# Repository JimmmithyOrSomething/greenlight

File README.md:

greenlight quantum number genorator

I've always been so interested in how nothing in our world is truly random but we still can never predict everything about any situation beucase all our information is relative. And I've always found it so cool how things on a quantum scale don't have to follow the same rules that we do like existing in one place at a time or needing a reason for something to happen. I built greenlight to show myself a little bit about how existance really works by generating a truly random number using a beam of light.

This is a quantum number generator, basically because nothing in our world can be random on a large scale this is a device that uses a beam of light split into two via a special panel which means exactly half of the photons go one way and half go the other. This means that when one photon hits the panel it both goes through and bounces off (existing in a super position)until it is read by one of the photo diodes at which point that position becomes real (like schrodinger's cat but with light instead of a sensor looking for decay) And this can generate a fully random number that no computer could ever guess because it doesn’t follow our idea of cause and effect.

| item | quantity | price(total)  | info | link
| ------- | --- | --- |--- | --- |
| laser | 1 | 2  |The brains of the system| [here](https://www.aliexpress.us/item/3256808453111185.html?spm=a2g0o.productlist.main.35.744fqgtvqgtvPm&algo_pvid=f6886ff8-4b31-4075-8188-40aaf95708aa&algo_exp_id=f6886ff8-4b31-4075-8188-40aaf95708aa-34&pdp_ext_f=%7B%22order%22%3A%22-1%22%2C%22eval%22%3A%221%22%7D&pdp_npi=4%40dis%21USD%212.03%212.03%21%21%212.03%212.03%21%402101c72a17529456784327303e85bb%2112000046054694972%21sea%21US%210%21ABX&curPageLogUid=kv1oggH1eqMu&utparam-url=scene%3Asearch%7Cquery_from%3A) |
| photodioed|	5|	1|	Cheap photdiodes|	[here](https://www.aliexpress.us/item/3256806716614140.html?src=bing&aff_short_key=UneMJZVf&aff_platform=true&isdl=y&albch=shopping&acnt=135095331&isdl=y&albcp=555334313&albag=1297424920872946&slnk=&trgt=pla-2332888796630869&plac=&crea=81089116576383&netw=o&device=c&mtctp=e&utm_source=Bing&utm_medium=shopping&utm_campaign=PA_Bing_US_Pmax_Electronic_maxvalue_20250304_newstore&utm_content=US-ALL&utm_term=photodioed%20BPW34&msclkid=646af2a3190b163feb729ad8ca68c24f&gatewayAdapt=glo2usa)|
|PCB	|5|	23|	holds all my parts|	[here](https://jlcpcb.com/)|
|OP amp|	5|	6	|to make sure signal is readable|	[here](https://www.aliexpress.us/item/3256808626573500.html?spm=a2g0o.productlist.main.2.342a2183yR25hE&algo_pvid=02a50136-7563-4f8f-b229-f992b53c9055&algo_exp_id=02a50136-7563-4f8f-b229-f992b53c9055-1&pdp_ext_f=%7B%22order%22%3A%222%22%2C%22eval%22%3A%221%22%7D&pdp_npi=4%40dis%21USD%215.80%215.80%21%21%215.80%215.80%21%402103205117529457957094127e6313%2112000046772434171%21sea%21US%210%21ABX&curPageLogUid=N1vaMkOQOGpw&utparam-url=scene%3Asearch%7Cquery_from%3A)|
|filter|	1	|18 |	cheapest filter I can fild|	[here](https://www.amazon.com/Concept-ND1000000-20-Stops-Multi-Layer-Coatings/dp/B0CW3D2PMC/ref=sr_1_1_sspa?adgrpid=1332609823086002&dib=eyJ2IjoiMSJ9.GbUoWurGez8xOJK7iHyZM6mhiLBdfH48SLrOkIF-YmTWcl3uBkbn52Y6AGVJasMP8Lmqf6YZ6I2f6fziKpwVHIBvxAwMenP9v0XX4e_BqgdHE4egFfyvJ2jyUc7t6Rfa1wY0C-v8xH4QZoVuCoLrwVx_2d1sE8cAqdTrmQmJrvVp6806LEs6a12m2_RrR0SjqPXmmdagr7ZUKq4f7kg7F52Zq2PsGZmk6Sk268Yzays.Db1pMk2CLClHrpgIouHmAGj_aQwpIjryEDxz2_Z2RQA&dib_tag=se&hvadid=83288427977273&hvbmt=be&hvdev=c&hvlocphy=103047&hvnetw=o&hvqmt=e&hvtargid=kwd-83289171702520%3Aloc-190&hydadcr=7692_13723063&keywords=20%2Bstop%2Bnd%2Bfilter&mcid=c65c21dc498d3d9291255622b3970efc&msclkid=84e1ac82a5c812d00597c4f970b71ac8&qid=1752946051&sr=8-1-spons&sp_csd=d2lkZ2V0TmFtZT1zcF9hdGY&th=1)|

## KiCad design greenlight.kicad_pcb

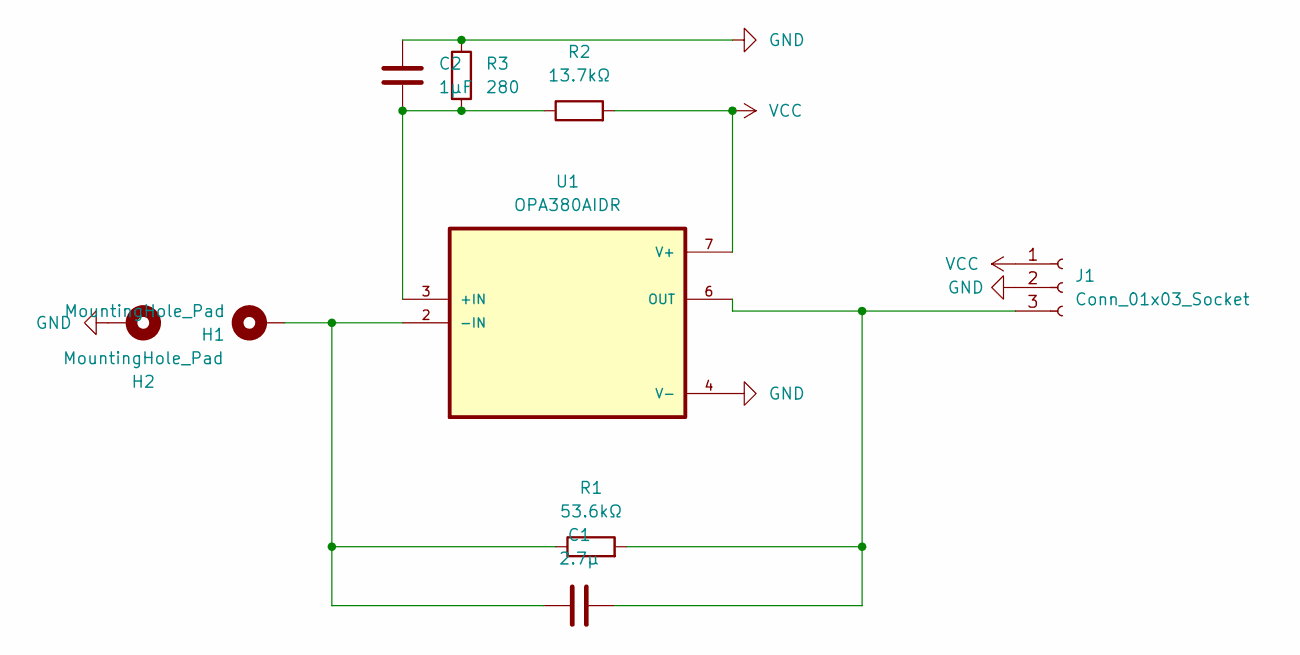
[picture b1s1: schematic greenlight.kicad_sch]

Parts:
C1: 2.7µ; C_0805_2012Metric_Pad1.18x1.45mm_HandSolder
C2: 1µF; C_0805_2012Metric_Pad1.18x1.45mm_HandSolder
H1, H2: MountingHole_Pad; MountingHole_2.5mm_Pad
J1: Conn_01x03_Socket; PinHeader_1x03_P1.00mm_Horizontal
R1: 53.6kΩ; R_0805_2012Metric_Pad1.20x1.40mm_HandSolder
R2: 13.7kΩ; R_0805_2012Metric_Pad1.20x1.40mm_HandSolder
R3: 280; R_0805_2012Metric_Pad1.20x1.40mm_HandSolder
U1: OPA380AIDR; SOIC127P599X175-8N

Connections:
GND: C2.2, H2.1, J1.2, R3.1, U1.4 (V-)
unnamed: C1.2, J1.3, R1.2, U1.6 (OUT)
unnamed: C2.1, R2.1, R3.2, U1.3 (+IN)
unnamed: C1.1, H1.1, R1.1, U1.2 (-IN)
VCC: J1.1, R2.2, U1.7 (V+)

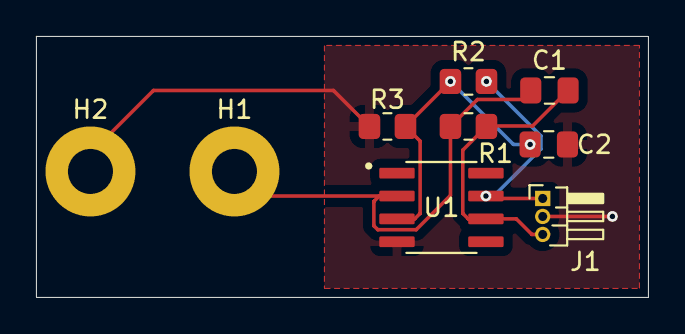
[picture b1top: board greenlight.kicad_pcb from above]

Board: 2 copper layers, 34.0 x 14.5 mm, 9 parts (0 on the bottom side), 5 nets.

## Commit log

2025-07-19 Rename greenlight v2.f3d to CAD/greenlight v2.f3d
2025-07-19 Rename greenlight.kicad_pro to PCB/greenlight.kicad_pro
2025-08-06 Rename greenlight.step to greenlight.step
